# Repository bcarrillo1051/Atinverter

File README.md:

# Atinverter
Open Source DC to AC Inverter Documentation: https://bcarrillo1051.github.io/Atinverter/

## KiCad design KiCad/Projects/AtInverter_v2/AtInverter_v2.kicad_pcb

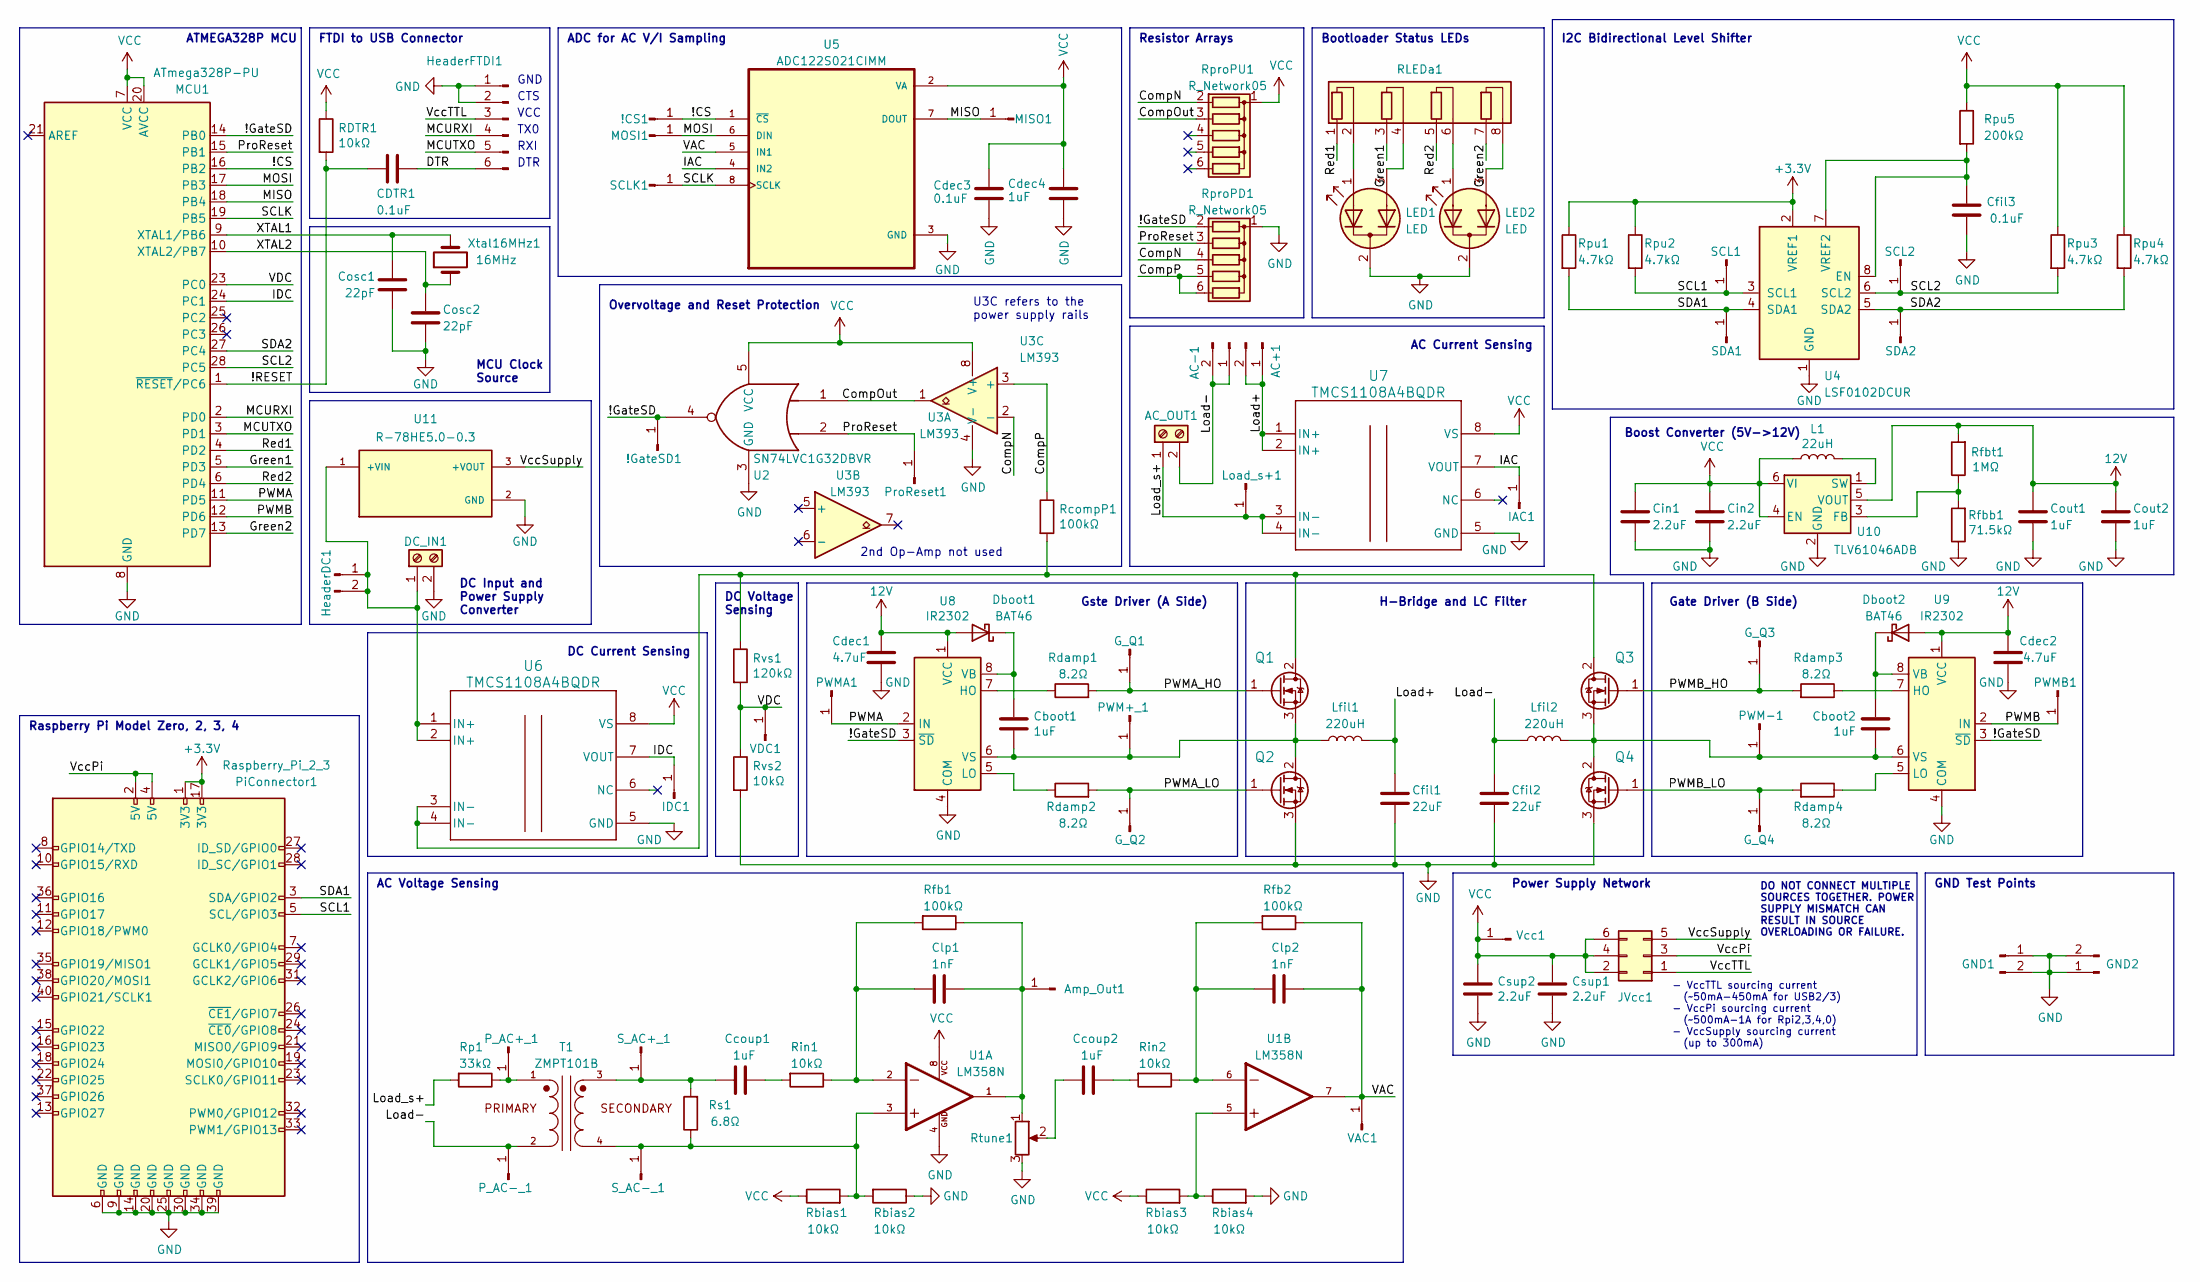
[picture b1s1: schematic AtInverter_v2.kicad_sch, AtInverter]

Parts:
!CS1: Conn_01x01_Male; PinHeader_1x01_P2.54mm_Vertical
!GateSD1: Conn_01x01_Male; PinHeader_1x01_P2.54mm_Vertical
AC+1: Conn_01x02_Pin; PinHeader_1x02_P2.54mm_Vertical
AC-1: Conn_01x02_Pin; PinHeader_1x02_P2.54mm_Vertical
AC_OUT1: Screw_Terminal_01x02; Term_Block_1x2_P5mm
Amp_Out1: Conn_01x01_Male; PinHeader_1x01_P2.54mm_Vertical
CDTR1: 0.1uF; C_1206_3216Metric
Cboot1, Cboot2: 1uF; C_0805_2012Metric
Ccoup1, Ccoup2: 1uF; C_1206_3216Metric
Cdec1, Cdec2: 4.7uF; C_1206_3216Metric
Cdec3: 0.1uF; C_0805_2012Metric
Cdec4: 1uF; C_0805_2012Metric
Cfil1, Cfil2: 22uF; CAP_BX_10x16_RUB
Cfil3: 0.1uF; C_1206_3216Metric
Cin1, Cin2: 2.2uF; C_0805_2012Metric
Clp1, Clp2: 1nF; C_1206_3216Metric
Cosc1, Cosc2: 22pF; C_1206_3216Metric
Cout1, Cout2: 1uF; C_0805_2012Metric
Csup1, Csup2: 2.2uF; C_1206_3216Metric
DC_IN1: Screw_Terminal_01x02; Term_Block_1x2_P5mm
Dboot1, Dboot2: BAT46; D_SOD-123
GND1, GND2: Conn_01x02_Pin; PinHeader_1x02_P2.54mm_Vertical
G_Q1, G_Q2, G_Q3, G_Q4: Conn_01x01_Male; PinHeader_1x01_P2.54mm_Vertical
HeaderDC1: Conn_01x02_Pin; PinHeader_1x02_P2.54mm_Vertical
HeaderFTDI1: Conn_01x06_Male; FTDI_USB_TTL_Header
IAC1: Conn_01x01_Male; PinHeader_1x01_P2.54mm_Vertical
IDC1: Conn_01x01_Male; PinHeader_1x01_P2.54mm_Vertical
JVcc1: Conn_02x03_Odd_Even; PinHeader_2x03_P2.54mm_Vertical
L1: 22uH; IND_BOURNS_SDR0403
LED1, LED2: LED; LED_3pin_P2.54mm
Lfil1, Lfil2: 220uH; AIRD-02_ABR
Load_s+1: Conn_01x01_Male; PinHeader_1x01_P2.54mm_Vertical
MCU1: ATmega328P-PU; DIP-28_W7.62mm_Socket
MISO1: Conn_01x01_Male; PinHeader_1x01_P2.54mm_Vertical
MOSI1: Conn_01x01_Male; PinHeader_1x01_P2.54mm_Vertical
PWM+_1: Conn_01x01_Male; PinHeader_1x01_P2.54mm_Vertical
PWM-1: Conn_01x01_Male; PinHeader_1x01_P2.54mm_Vertical
PWMA1: Conn_01x01_Male; PinHeader_1x01_P2.54mm_Vertical
PWMB1: Conn_01x01_Male; PinHeader_1x01_P2.54mm_Vertical
P_AC+_1: Conn_01x01_Male; PinHeader_1x01_P2.54mm_Vertical
P_AC-_1: Conn_01x01_Male; PinHeader_1x01_P2.54mm_Vertical
PiConnector1: Raspberry_Pi_2_3; Raspberry_Pi_Zero_and_Four
ProReset1: Conn_01x01_Male; PinHeader_1x01_P2.54mm_Vertical
Q1, Q2, Q3, Q4: IRFB4020PBF; TO-220-3_Vertical; MPN IRF540NPBF; Digi-Key_PN IRF540NPBF-ND
RDTR1: 10kΩ; R_1206_3216Metric
RLEDa1: R_Array; R_Array_SIP8
Rbias1, Rbias2, Rbias3, Rbias4: 10kΩ; R_1206_3216Metric
RcompP1: 100kΩ; R_1206_3216Metric
Rdamp1, Rdamp2, Rdamp3, Rdamp4: 8.2Ω; R_1206_3216Metric
Rfb1, Rfb2: 100kΩ; R_1206_3216Metric
Rfbb1: 71.5kΩ; R_0805_2012Metric
Rfbt1: 1MΩ; R_0805_2012Metric
Rin1, Rin2: 10kΩ; R_1206_3216Metric
Rp1: 33kΩ; R_1206_3216Metric
RproPD1: R_Network05; R_Array_SIP6
RproPU1: R_Network05; R_Array_SIP6
Rpu1, Rpu2, Rpu3, Rpu4: 4.7kΩ; R_1206_3216Metric
Rpu5: 200kΩ; R_1206_3216Metric
Rs1: 6.8Ω; R_1206_3216Metric
Rtune1: R_Potentiometer; TC33X-2-104E_BRN
Rvs1: 120kΩ; R_1206_3216Metric
Rvs2: 10kΩ; R_1206_3216Metric
SCL1, SCL2: Conn_01x01_Male; PinHeader_1x01_P2.54mm_Vertical
SCLK1: Conn_01x01_Male; PinHeader_1x01_P2.54mm_Vertical
SDA1, SDA2: Conn_01x01_Male; PinHeader_1x01_P2.54mm_Vertical
S_AC+_1: Conn_01x01_Male; PinHeader_1x01_P2.54mm_Vertical
S_AC-_1: Conn_01x01_Male; PinHeader_1x01_P2.54mm_Vertical
T1: ZMPT101B; XFMR_ZMPT101B; PARTREV NA
U1: LM358N; D8; PARTREV 1.0.3
U2: SN74LVC1G32DBVR; DBV5
U3: LM393; SO8_STM
U4: LSF0102DCUR; DCU0008A_L
U5: ADC122S021CIMM; MUA08A
U6, U7: TMCS1108A4BQDR; D0008A-IPC_A
U8, U9: IR2302; PG-DSO-8-910_INF
U10: TLV61046ADB; SOT-23-6
U11: R-78HE5.0-0.3; R-78HE-0.3_SIP3_11.5X8.5X12.5_RCP; PARTREV 0/2019
VAC1: Conn_01x01_Male; PinHeader_1x01_P2.54mm_Vertical
VDC1: Conn_01x01_Male; PinHeader_1x01_P2.54mm_Vertical
Vcc1: Conn_01x01_Male; PinHeader_1x01_P2.54mm_Vertical
Xtal16MHz1: 16MHz; Resonator-2Pin_W10.0mm_H5.0mm

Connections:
12V: Cdec1.1, Cdec2.1, Cout1.1, Cout2.1, Dboot1.2 (A), Dboot2.2 (A), Rfbt1.2, U8.1 (VCC), U9.1 (VCC), U10.5 (VOUT)
+3.3V: PiConnector1.1 (3V3), PiConnector1.17 (3V3), Rpu1.1, Rpu2.1, U4.2 (VREF1)
/!CS: !CS1.1, MCU1.16 (PB2), U5.1 (~CS)
/!GateSD: !GateSD1.1, MCU1.14 (PB0), RproPD1.2 (R1), U2.4, U8.3 (~SD), U9.3 (~SD)
/!RESET: CDTR1.2, MCU1.1 (~RESET/PC6), RDTR1.2
/CompN: RproPD1.4 (R3), RproPU1.2 (R1), U3.2 (-)
/CompOut: RproPU1.3 (R2), U2.1, U3.1
/CompP: RcompP1.1, RproPD1.5 (R4), RproPD1.6 (R5), U3.3 (+)
/DTR: CDTR1.1, HeaderFTDI1.6
/Green1: MCU1.5 (PD3), RLEDa1.3 (R2.1)
/Green2: MCU1.13 (PD7), RLEDa1.7 (R4.1)
/IAC: IAC1.1, U5.4 (IN2), U7.7 (VOUT)
/IDC: IDC1.1, MCU1.24 (PC1), U6.7 (VOUT)
/Load+: AC+1.1, AC+1.2, Cfil1.1, Lfil1.2, U7.1 (IN+), U7.2 (IN+)
/Load-: AC-1.1, AC-1.2, AC_OUT1.2, Cfil2.1, Lfil2.1, P_AC-_1.1, T1.2
/Load_s+: AC_OUT1.1, Load_s+1.1, Rp1.2, U7.3 (IN-), U7.4 (IN-)
/MCURXI: HeaderFTDI1.4, MCU1.2 (PD0)
/MCUTXO: HeaderFTDI1.5, MCU1.3 (PD1)
/MISO: MCU1.18 (PB4), MISO1.1, U5.7 (DOUT)
/MOSI: MCU1.17 (PB3), MOSI1.1, U5.6 (DIN)
/PWMA: MCU1.11 (PD5), PWMA1.1, U8.2 (IN)
/PWMA_HO: G_Q1.1, Q1.1 (G), Rdamp1.2
/PWMA_LO: G_Q2.1, Q2.1 (G), Rdamp2.2
/PWMB: MCU1.12 (PD6), PWMB1.1, U9.2 (IN)
/PWMB_HO: G_Q3.1, Q3.1 (G), Rdamp3.2
/PWMB_LO: G_Q4.1, Q4.1 (G), Rdamp4.2
/ProReset: MCU1.15 (PB1), ProReset1.1, RproPD1.3 (R2), U2.2
/Red1: MCU1.4 (PD2), RLEDa1.1 (R1.1)
/Red2: MCU1.6 (PD4), RLEDa1.5 (R3.1)
/SCL1: PiConnector1.5 (SCL/GPIO3), Rpu2.2, SCL1.1, U4.3 (SCL1)
/SCL2: MCU1.28 (PC5), Rpu3.2, SCL2.1, U4.6 (SCL2)
/SCLK: MCU1.19 (PB5), SCLK1.1, U5.8 (SCLK)
/SDA1: PiConnector1.3 (SDA/GPIO2), Rpu1.2, SDA1.1, U4.4 (SDA1)
/SDA2: MCU1.27 (PC4), Rpu4.2, SDA2.1, U4.5 (SDA2)
/VAC: Clp2.1, Rfb2.1, U1.7, U5.5 (IN1), VAC1.1
/VDC: MCU1.23 (PC0), Rvs1.2, Rvs2.1, VDC1.1
/VccPi: JVcc1.3, PiConnector1.2 (5V), PiConnector1.4 (5V)
/VccSupply: JVcc1.5, U11.3 (+VOUT)
/VccTTL: HeaderFTDI1.3, JVcc1.1
/XTAL1: Cosc1.2, MCU1.9 (XTAL1/PB6), Xtal16MHz1.2
/XTAL2: Cosc2.1, MCU1.10 (XTAL2/PB7), Xtal16MHz1.1
GND: Cdec1.2, Cdec2.2, Cdec3.2, Cdec4.2, Cfil1.2, Cfil2.2, Cfil3.1, Cin1.2, Cin2.2, Cosc1.1, Cosc2.2, Cout1.2, Cout2.2, Csup1.2, Csup2.2, DC_IN1.2, GND1.1, GND1.2, GND2.1, GND2.2, HeaderFTDI1.1, HeaderFTDI1.2, LED1.2 (K), LED2.2 (K), MCU1.8 (GND), MCU1.22 (GND), PiConnector1.6 (GND), PiConnector1.9 (GND), PiConnector1.14 (GND), PiConnector1.20 (GND), PiConnector1.25 (GND), PiConnector1.30 (GND), PiConnector1.34 (GND), PiConnector1.39 (GND), Q2.3 (S), Q4.3 (S), Rbias2.1, Rbias4.2, Rfbb1.1, RproPD1.1 (common), Rtune1.3, Rvs2.2, U1.4, U2.3 (GND), U3.4 (V-), U4.1 (GND), U5.3 (GND), U6.5 (GND), U7.5 (GND), U8.4 (COM), U9.4 (COM), U10.2 (GND), U11.2 (GND)
unnamed: Amp_Out1.1, Clp1.1, Rfb1.1, Rtune1.1, U1.1
unnamed: Ccoup1.1, Rin1.2
unnamed: Ccoup2.1, Rin2.2
unnamed: Ccoup2.2, Rtune1.2
unnamed: Clp1.2, Rfb1.2, Rin1.1, U1.2
unnamed: Clp2.2, Rfb2.2, Rin2.1, U1.6
unnamed: DC_IN1.1, HeaderDC1.1, HeaderDC1.2, U6.1 (IN+), U6.2 (IN+), U11.1 (+VIN)
unnamed: Cboot1.1, Dboot1.1 (K), U8.8 (VB)
unnamed: Cboot2.1, Dboot2.1 (K), U9.8 (VB)
unnamed: LED1.1 (A1), RLEDa1.2 (R1.2)
unnamed: LED1.3 (A2), RLEDa1.4 (R2.2)
unnamed: LED2.1 (A1), RLEDa1.6 (R3.2)
unnamed: LED2.3 (A2), RLEDa1.8 (R4.2)
unnamed: Cboot1.2, Lfil1.1, PWM+_1.1, Q1.3 (S), Q2.2 (D), U8.6 (VS)
unnamed: Cboot2.2, Lfil2.2, PWM-1.1, Q3.3 (S), Q4.2 (D), U9.6 (VS)
unnamed: P_AC+_1.1, Rp1.1, T1.1
unnamed: Q1.2 (D), Q3.2 (D), RcompP1.2, Rvs1.1, U6.3 (IN-), U6.4 (IN-)
unnamed: Rbias3.2, Rbias4.1, U1.5
unnamed: Ccoup1.2, Rs1.2, S_AC+_1.1, T1.3
unnamed: Rbias1.2, Rbias2.2, Rs1.1, S_AC-_1.1, T1.4, U1.3
unnamed: Cfil3.2, Rpu5.2, U4.7 (VREF2), U4.8 (EN)
unnamed: Rdamp1.1, U8.7 (HO)
unnamed: Rdamp2.1, U8.5 (LO)
unnamed: Rdamp3.1, U9.7 (HO)
unnamed: Rdamp4.1, U9.5 (LO)
unnamed: Rfbb1.2, Rfbt1.1, U10.3 (FB)
unnamed: L1.2, U10.1 (SW)
VCC: Cdec3.1, Cdec4.1, Cin1.1, Cin2.1, Csup1.1, Csup2.1, JVcc1.2, JVcc1.4, JVcc1.6, L1.1, MCU1.7 (VCC), MCU1.20 (AVCC), RDTR1.1, Rbias1.1, Rbias3.1, RproPU1.1 (common), Rpu3.1, Rpu4.1, Rpu5.1, U1.8, U2.5 (VCC), U3.8 (V+), U5.2 (VA), U6.8 (VS), U7.8 (VS), U10.4 (EN), U10.6 (VI), Vcc1.1

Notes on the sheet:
RXI
MCU Clock Source
ADC for AC V/I Sampling
AC Current Sensing
Overvoltage and Reset Protection
Power Supply Network
Boost Converter (5V->12V)
GND
ATMEGA328P MCU
Raspberry Pi Model Zero, 2, 3, 4
VCC
FTDI to USB Connector
DC Voltage Sensing
DO NOT CONNECT MULTIPLE SOURCES TOGETHER. POWER SUPPLY MISMATCH CAN RESULT IN SOURCE OVERLOADING OR FAILURE.
TX0
H-Bridge and LC Filter
AC Voltage Sensing
I2C Bidirectional Level Shifter
Gate Driver (B Side)
U3C refers to the power supply rails
DC Input and Power Supply Converter
- VccTTL sourcing current (~50mA-450mA for USB2/3) - VccPi sourcing current (~500mA-1A for Rpi2,3,4,0) - VccSupply sourcing current (up to 300mA)
DTR
Bootloader Status LEDs
CTS
2nd Op-Amp not used
Resistor Arrays
DC Current Sensing
GND Test Points
Gste Driver (A Side)

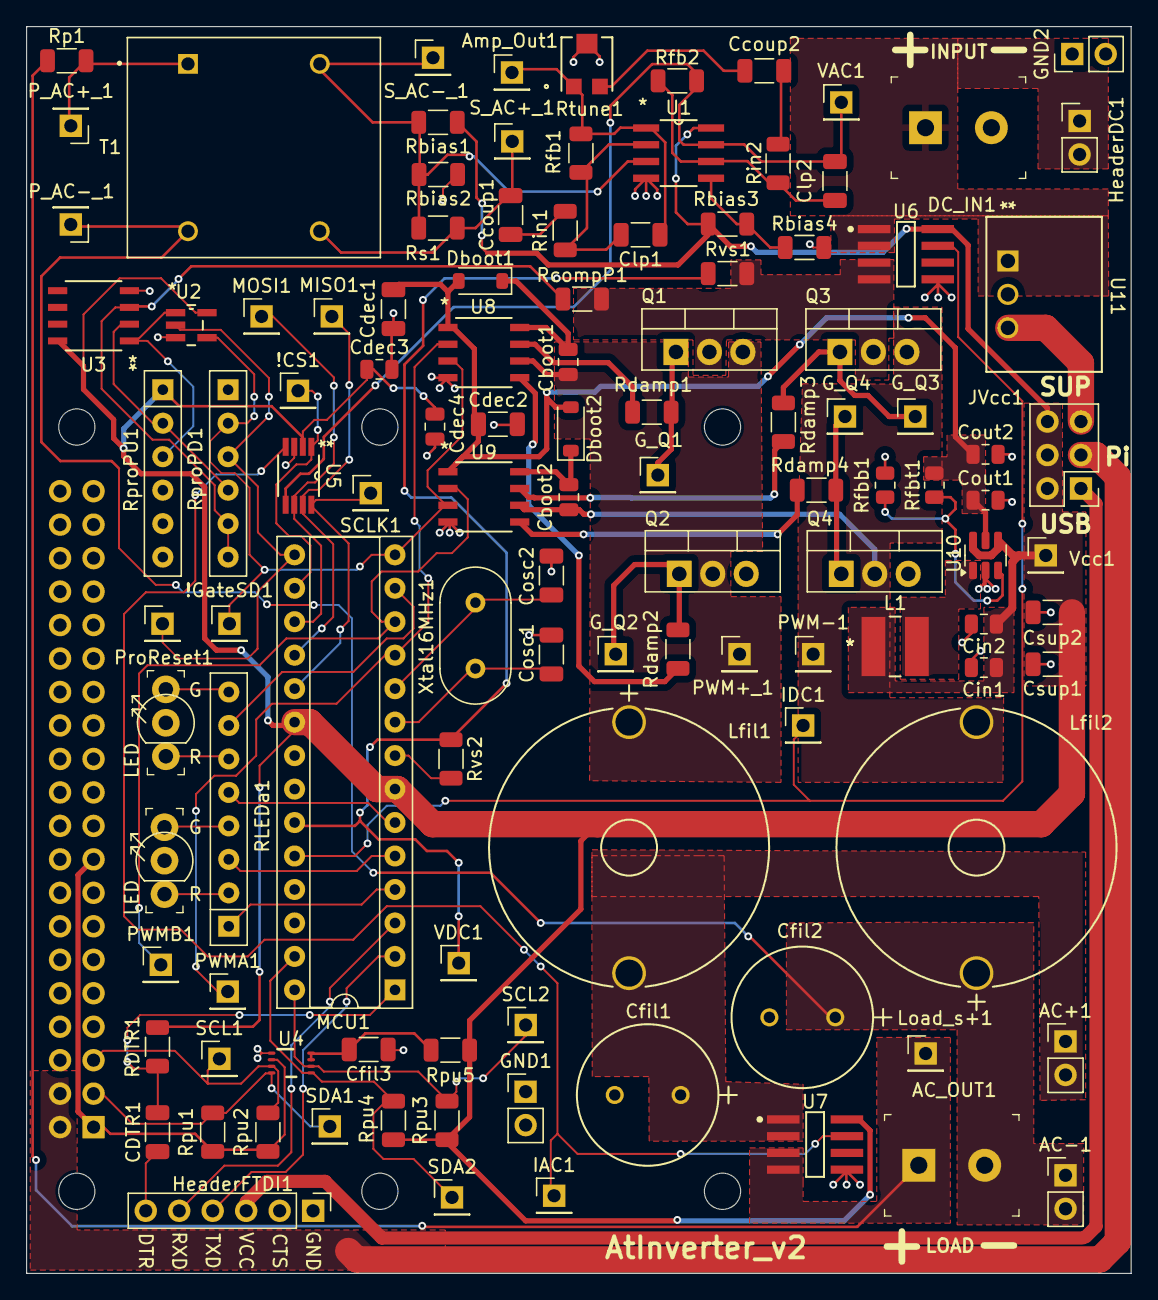
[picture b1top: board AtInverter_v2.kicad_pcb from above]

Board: 2 copper layers, 83.8 x 94.6 mm, 115 parts (1 on the bottom side), 70 nets.

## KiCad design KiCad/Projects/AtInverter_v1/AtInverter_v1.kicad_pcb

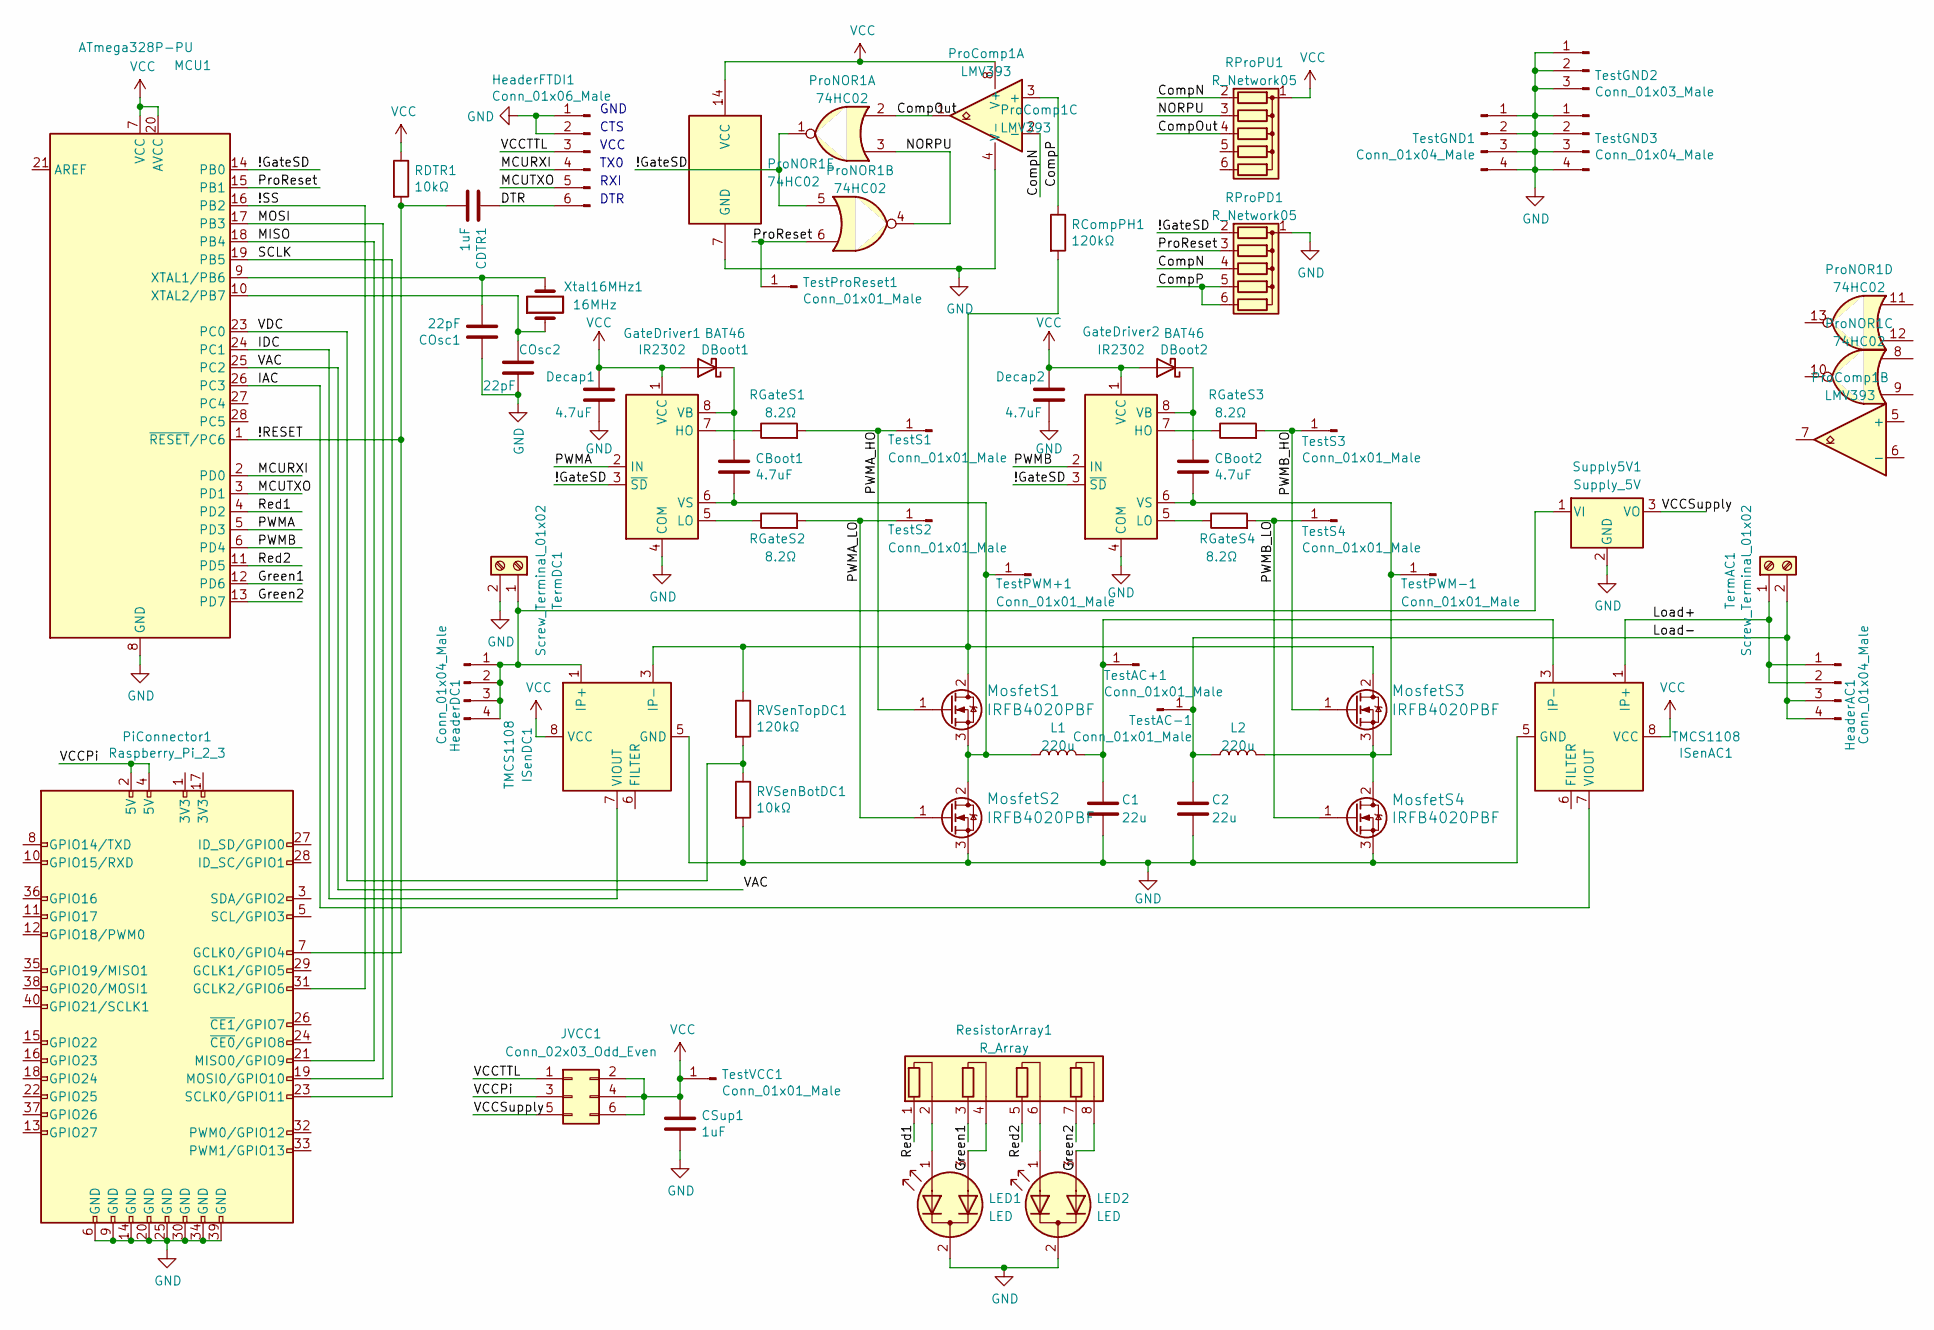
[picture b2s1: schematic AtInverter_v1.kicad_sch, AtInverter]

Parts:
C1, C2: 22u; CAP_BX_10x16_RUB
CBoot1, CBoot2: 4.7uF; C_Rect_L7.2mm_W3.5mm_P5.00mm_FKS2_FKP2_MKS2_MKP2
CDTR1: 1uF; C_Rect_L7.2mm_W3.5mm_P5.00mm_FKS2_FKP2_MKS2_MKP2
COsc1, COsc2: 22pF; C_Rect_L7.2mm_W3.5mm_P5.00mm_FKS2_FKP2_MKS2_MKP2
CSup1: 1uF; C_Rect_L7.2mm_W3.5mm_P5.00mm_FKS2_FKP2_MKS2_MKP2
DBoot1, DBoot2: BAT46; D_DO-35_SOD27_P7.62mm_Horizontal
Decap1, Decap2: 4.7uF; CAP_FG28_TDK
GateDriver1, GateDriver2: IR2302; DIP-8_W7.62mm_LongPads
HeaderAC1: Conn_01x04_Male; PinHeader_1x04_P2.54mm_Vertical
HeaderDC1: Conn_01x04_Male; PinHeader_1x04_P2.54mm_Vertical
HeaderFTDI1: Conn_01x06_Male; FTDI_USB_TTL_Header
ISenAC1: TMCS1108; SOIC-8_3.9x4.9mm_P1.27mm
ISenDC1: TMCS1108; SOIC-8_3.9x4.9mm_P1.27mm
JVCC1: Conn_02x03_Odd_Even; PinHeader_2x03_P2.54mm_Vertical
L1, L2: 220u; AIRD-02_ABR
LED1, LED2: LED; LED_3pin_P2.54mm
MCU1: ATmega328P-PU; DIP-28_W7.62mm
MosfetS1, MosfetS2, MosfetS3, MosfetS4: IRFB4020PBF; TO-220-3_Vertical; MPN IRF540NPBF; Digi-Key_PN IRF540NPBF-ND
PiConnector1: Raspberry_Pi_2_3; Raspberry_Pi_Zero_and_Four
ProComp1: LMV393; DIP-8_W7.62mm_LongPads
ProNOR1: 74HC02; DIP-14_W7.62mm_LongPads
RCompPH1: 120kΩ; R_Axial_DIN0207_L6.3mm_D2.5mm_P7.62mm_Horizontal
RDTR1: 10kΩ; R_Axial_DIN0207_L6.3mm_D2.5mm_P7.62mm_Horizontal
RGateS1, RGateS2, RGateS3, RGateS4: 8.2Ω; R_Axial_DIN0207_L6.3mm_D2.5mm_P7.62mm_Horizontal
RProPD1: R_Network05; R_Array_SIP6
RProPU1: R_Network05; R_Array_SIP6
RVSenBotDC1: 10kΩ; R_Axial_DIN0207_L6.3mm_D2.5mm_P7.62mm_Horizontal
RVSenTopDC1: 120kΩ; R_Axial_DIN0207_L6.3mm_D2.5mm_P7.62mm_Horizontal
ResistorArray1: R_Array; R_Array_SIP8
Supply5V1: Supply_5V; SupplyDC_48V-5V_TO-220-3_Vertical
TermAC1: Screw_Terminal_01x02; Term_Block_1x2_P5mm
TermDC1: Screw_Terminal_01x02; Term_Block_1x2_P5mm
TestAC+1: Conn_01x01_Male; PinHeader_1x01_P2.54mm_Vertical
TestAC-1: Conn_01x01_Male; PinHeader_1x01_P2.54mm_Vertical
TestGND1, TestGND3: Conn_01x04_Male; PinHeader_1x04_P2.54mm_Vertical
TestGND2: Conn_01x03_Male; PinHeader_1x03_P2.54mm_Vertical
TestPWM+1: Conn_01x01_Male; PinHeader_1x01_P2.54mm_Vertical
TestPWM-1: Conn_01x01_Male; PinHeader_1x01_P2.54mm_Vertical
TestProReset1: Conn_01x01_Male; PinHeader_1x01_P2.54mm_Vertical
TestS1, TestS2, TestS3, TestS4: Conn_01x01_Male; PinHeader_1x01_P2.54mm_Vertical
TestVCC1: Conn_01x01_Male; PinHeader_1x01_P2.54mm_Vertical
Xtal16MHz1: 16MHz; Resonator-2Pin_W10.0mm_H5.0mm

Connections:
/!GateSD: GateDriver1.3 (~SD), GateDriver2.3 (~SD), MCU1.14 (PB0), ProNOR1.1, ProNOR1.5, RProPD1.2 (R1)
/!RESET: CDTR1.2, MCU1.1 (~RESET/PC6), PiConnector1.7 (GCLK0/GPIO4), RDTR1.2
/!SS: MCU1.16 (PB2), PiConnector1.31 (GCLK2/GPIO6)
/CompN: ProComp1.2 (-), RProPD1.4 (R3), RProPU1.2 (R1)
/CompOut: ProComp1.1, ProNOR1.2, RProPU1.4 (R3)
/CompP: ProComp1.3 (+), RCompPH1.1, RProPD1.5 (R4), RProPD1.6 (R5); also elsewhere on the board
/DTR: CDTR1.1, HeaderFTDI1.6
/Green1: MCU1.12 (PD6), ResistorArray1.3 (R2.1)
/Green2: MCU1.13 (PD7), ResistorArray1.7 (R4.1)
/IAC: ISenAC1.7 (VIOUT), MCU1.26 (PC3)
/IDC: ISenDC1.7 (VIOUT), MCU1.24 (PC1)
/Load+: HeaderAC1.1, HeaderAC1.2, ISenAC1.1 (IP+), ISenAC1.2 (IP+), TermAC1.1
/Load-: C2.1, HeaderAC1.3, HeaderAC1.4, L2.1, TermAC1.2, TestAC-1.1
/MCURXI: HeaderFTDI1.4, MCU1.2 (PD0)
/MCUTXO: HeaderFTDI1.5, MCU1.3 (PD1)
/MISO: MCU1.18 (PB4), PiConnector1.21 (MISO0/GPIO9)
/MOSI: MCU1.17 (PB3), PiConnector1.19 (MOSI0/GPIO10)
/NORPU: ProNOR1.3, ProNOR1.4, RProPU1.3 (R2)
/PWMA: GateDriver1.2 (IN), MCU1.5 (PD3)
/PWMA_HO: MosfetS1.1 (G), RGateS1.2, TestS1.1
/PWMA_LO: MosfetS2.1 (G), RGateS2.2, TestS2.1
/PWMB: GateDriver2.2 (IN), MCU1.6 (PD4)
/PWMB_HO: MosfetS3.1 (G), RGateS3.2, TestS3.1
/PWMB_LO: MosfetS4.1 (G), RGateS4.2, TestS4.1
/ProReset: MCU1.15 (PB1), ProNOR1.6, RProPD1.3 (R2), TestProReset1.1
/Red1: MCU1.4 (PD2), ResistorArray1.1 (R1.1)
/Red2: MCU1.11 (PD5), ResistorArray1.5 (R3.1)
/SCLK: MCU1.19 (PB5), PiConnector1.23 (SCLK0/GPIO11)
/VAC: MCU1.25 (PC2)
/VCCPi: JVCC1.3, PiConnector1.2 (5V), PiConnector1.4 (5V)
/VCCSupply: JVCC1.5, Supply5V1.3 (VO)
/VCCTTL: HeaderFTDI1.3, JVCC1.1
/VDC: MCU1.23 (PC0), RVSenBotDC1.1, RVSenTopDC1.2
GND: C1.2, C2.2, COsc1.1, COsc2.2, CSup1.2, Decap1.2, Decap2.2, GateDriver1.4 (COM), GateDriver2.4 (COM), HeaderFTDI1.1, HeaderFTDI1.2, ISenAC1.5 (GND), ISenDC1.5 (GND), LED1.2 (K), LED2.2 (K), MCU1.8 (GND), MCU1.22 (GND), MosfetS2.3 (S), MosfetS4.3 (S), PiConnector1.6 (GND), PiConnector1.9 (GND), PiConnector1.14 (GND), PiConnector1.20 (GND), PiConnector1.25 (GND), PiConnector1.30 (GND), PiConnector1.34 (GND), PiConnector1.39 (GND), ProComp1.4 (V-), ProNOR1.7 (GND), RProPD1.1 (common), RVSenBotDC1.2, Supply5V1.2 (GND), TermDC1.2, TestGND1.1, TestGND1.2, TestGND1.3, TestGND1.4, TestGND2.1, TestGND2.2, TestGND2.3, TestGND3.1, TestGND3.2, TestGND3.3, TestGND3.4
unnamed: CBoot1.1, DBoot1.1 (K), GateDriver1.8 (VB)
unnamed: CBoot2.1, DBoot2.1 (K), GateDriver2.8 (VB)
unnamed: GateDriver1.7 (HO), RGateS1.1
unnamed: GateDriver1.5 (LO), RGateS2.1
unnamed: CBoot1.2, GateDriver1.6 (VS), L1.1, MosfetS1.3 (S), MosfetS2.2 (D), TestPWM+1.1
unnamed: GateDriver2.7 (HO), RGateS3.1
unnamed: GateDriver2.5 (LO), RGateS4.1
unnamed: CBoot2.2, GateDriver2.6 (VS), L2.2, MosfetS3.3 (S), MosfetS4.2 (D), TestPWM-1.1
unnamed: HeaderDC1.1, HeaderDC1.2, HeaderDC1.3, HeaderDC1.4, ISenDC1.1 (IP+), ISenDC1.2 (IP+), Supply5V1.1 (VI), TermDC1.1
unnamed: LED1.1 (A1), ResistorArray1.2 (R1.2)
unnamed: LED1.3 (A2), ResistorArray1.4 (R2.2)
unnamed: LED2.1 (A1), ResistorArray1.6 (R3.2)
unnamed: LED2.3 (A2), ResistorArray1.8 (R4.2)
unnamed: COsc1.2, MCU1.9 (XTAL1/PB6), Xtal16MHz1.2
unnamed: COsc2.1, MCU1.10 (XTAL2/PB7), Xtal16MHz1.1
unnamed 49: ISenDC1.3 (IP-), ISenDC1.4 (IP-), MosfetS1.2 (D), MosfetS3.2 (D), RCompPH1.2, RVSenTopDC1.1; also elsewhere on the board
unnamed: C1.1, ISenAC1.3 (IP-), ISenAC1.4 (IP-), L1.2, TestAC+1.1
VCC: CSup1.1, DBoot1.2 (A), DBoot2.2 (A), Decap1.1, Decap2.1, GateDriver1.1 (VCC), GateDriver2.1 (VCC), ISenAC1.8 (VCC), ISenDC1.8 (VCC), JVCC1.2, JVCC1.4, JVCC1.6, MCU1.7 (VCC), MCU1.20 (AVCC), ProComp1.8 (V+), ProNOR1.14 (VCC), RDTR1.1, RProPU1.1 (common), TestVCC1.1

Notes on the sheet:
RXI
GND
VCC
TX0
DTR
CTS

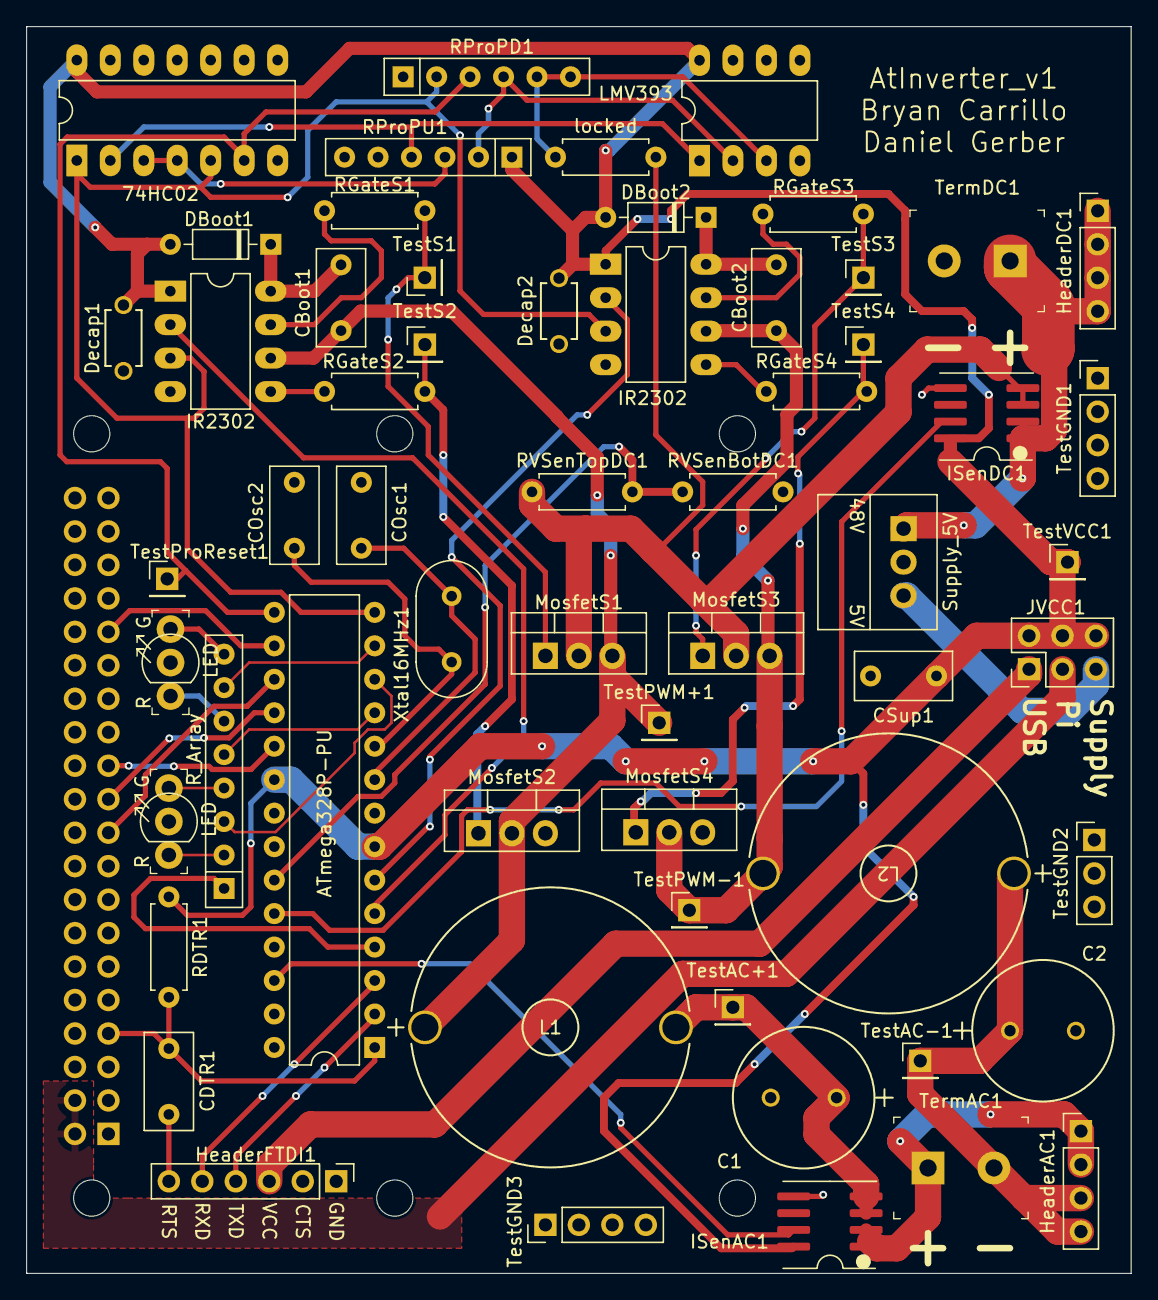
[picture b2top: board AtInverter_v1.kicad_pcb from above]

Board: 2 copper layers, 83.8 x 94.6 mm, 60 parts (1 on the bottom side), 51 nets.

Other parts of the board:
locked: 120kΩ; R_Axial_DIN0207_L6.3mm_D2.5mm_P7.62mm_Horizontal

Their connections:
/CompP: locked.1; also elsewhere on the board
unnamed 49: locked.2; also elsewhere on the board

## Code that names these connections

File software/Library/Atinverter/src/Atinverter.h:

/*
	Atinverter.h = Library for Atinverter pin and functions
  	Created by Bryan Carrillo, Zach Kwast, 10/18/24
	Released into the public domain (Open Source DC to AC Inverter)
*/

#ifndef ATINVERTER_H
#define ATINVERTER_H

#include <Arduino.h>
#include <SPI.h>

// --- TMCS1108 Current Sensor Parameters ---
#define SENSOR_GAIN_MV_PER_A 400.0f // Sensitivity for A4 variant (400 mV per A)
#define MV_TO_V 0.001f // Scaling factor from mV to V
#define VOUT_0A 2.5f // Zero current output voltage

// --- ADC Parameters ---
#define VREF 5.0f // Reference voltage for both ADCs
#define ADC_ATMEGA328P_MAX_VALUE 1023.0f // For ATMEGA328P (internal ADC)
#define ADC_122S021_MAX_VALUE 4095.0f // For ADC122S021 (external SPI ADC)
#define VAC_ADC_CHANNEL 0x00 // ADC122S021 channel 1
#define IAC_ADC_CHANNEL 0x08 // ADC122S021 channel 2
#define CLOCK_FREQUENCY 1000000 // Clock used to drive ADC122S021

// --- AC RMS Parameters ---
#define MS_PER_SECOND 1000 // For computing the sampling period in ms
#define DEFAULT_SENSITIVITY 500.0f // When no sensitivity is specified for AC RMS calculation
#define SENSITIVITY 38.12f // Tuned value after testing, adjust as needed

// --- Moving Average Parameter ---
#define MA_SAMPLES 10 // Default moving average sample count, adjust as needed

// --- PWM Inversion Parameters ---
#define SIN_50HZ_PWM_SIZE 313
#define SIN_60HZ_PWM_SIZE 260

// --- Safety Parameters ---
#define MAX_DC_CURRENT 2.5
#define MAX_AC_CURRENT 2.5

// shutdown error codes for convenience and bookkeeping. user-defined codes start at 4
enum ShutdownCodes
{
  // is not shut down = -1
  HARDWARE = 0,
  MANUAL = 1,
  OVERCURRENT = 2,
  OVERTEMPERATURE = 3,
  NUM_PRESETCODES
};

/**
 * @class Atinverter
 * @brief This class handles the control of the Atinverter, including pin setup
 *        and LED management.
 */
class Atinverter {

  public:
  	// - Constructor -

	Atinverter();

	// - Methods -

	// --- LED Blinking ---
	void setUpLEDs();
	void set1LED(int led, int state);
	void cycleLEDs(int t_delay);
	
	// --- DC Voltage and Current Sensing ---
	float getVdc();
	float getIdc();
	float getAvgDC(bool isVdc, float signalValue);

	// --- AC Voltage and Current Sensing ---
	void setUpSPI();
	void setSensitivity(float value);
	int getADC(uint8_t control_byte);
	float getRmsAC(bool isVac, uint8_t loopCount);

	// --- PWM 50Hz/60Hz Inversion ---
	void startPWM(uint16_t frequency);
	static void pwmISR();
	void enablePWM();
	void disablePWM();

	// --- Timer 2 Delay ---
	void initTimer2Delay();
	void delay2(unsigned long ms);
	unsigned long millis2();

	// --- Gate Shutdown ---
	void shutdownGates(int shutdownCode);
	void turnOnGates();
	void powerCycleGates();

	// --- Overcurrent Protection ---
	void checkOverCurrent(float dcCurrent, float acCurrent);

	// - Member Variables -

	// --- LED Blinking ---
	static const int LED1R_PIN = 2; // Red LED 1 pin | PD2
	static const int LED1G_PIN = 3; // Green LED 1 pin | PD3
	static const int LED2R_PIN = 4; // Red LED 2 pin | PD4
	static const int LED2G_PIN = 7; // Green LED 2 pin | PD7

	// --- Timer 2 Delay ---
	static volatile unsigned long timer2Millis; // Timer2 Increment

  private:

	// - Methods -

	// --- AC Voltage and Current Sensing ---
	int getZeroPoint(uint8_t control_byte);

	// - Member Variables -

	// --- AC Voltage and Current Sensing ---
	// Pin Definitions
	static const int VI_AC_CS_PIN = 10;   // SPI chip select pin | PB2
	static const int VI_AC_MOSI_PIN = 11; // Send control bits data pin | PB3
	static const int VI_AC_MISO_PIN = 12; // Receive AC output V/I sense pin | PB4
	static const int VI_AC_SCLK_PIN = 13; // SPI clock signal pin | PB5

	// Parameters AC Sensing
	uint32_t period; // Period of PWM type (50Hz or 60Hz)
	float 	 sensitivity = DEFAULT_SENSITIVITY; // Tune this value to achieve proper sensing

	// --- DC Voltage and Current Sensing ---
	// DC Voltage and Current Pin Definitions
	static const int V_DC_PIN = A0;           // DC input voltage sense pin | PC0
	static const int I_DC_PIN = A1;           // DC input current sense pin | PC1
	// DC Voltage Sensing Resistor Values
	static const unsigned long Rvs1 = 120000; // DC voltage sensing resistor 1, adjust as needed
	static const unsigned int Rsv2 = 9900;    // DC voltage sensing resistor 2, adjust as needed
	// Parameters for Vdc Moving Average
	static const int Vdc_num_readings = MA_SAMPLES; // Vdc samples in moving average
	float Vdc_readings[MA_SAMPLES];                 // Circular buffer for Vdc samples
	int Vdc_read_index = 0;                         // Current index in the Vdc buffer
	float Vdc_total = 0;                            // Running total of Vdc readings
	// Parameters for Idc Moving Average
	static const int Idc_num_readings = MA_SAMPLES; // Idc damples in moving average
	float Idc_readings[MA_SAMPLES];                 // Circular buffer for Idc samples
	int Idc_read_index = 0;                         // Current index in the Idc buffer
	float Idc_total = 0;                            // Running total of Idc readings

	// --- PWM 50Hz/60Hz Inversion ---
	// PWM Pin Definitions=
	const int PWM_A_PIN = 5;    // Positive half cycle PWM pin | PD5
	const int PWM_B_PIN = 6;    // Negative half cycle PWM pin | PD6
	const int GATESD_PIN = 8;   // Gate driver shut down mechanism pin | PB0
	const int PRORESET_PIN = 9; // Protection circuitry reset pin | PB1
	// Parameters for PWM
	static bool is50Hz;               // Frequency mode: true for 50Hz, false for 60Hz
	static int sin_i;                 // Index for sinPWM array value
	static int pwm_i;                 // Index for PWM value
	static int OK;                    // Flag to toggle between pins 5 and 6
	static const int sin50HzPWM[312]; // Sinusoidal 50Hz array samples
	static const int sin60HzPWM[261]; // Sinusoidal 60Hz array samples

	// --- I2C Communication ---
	const int I2C_SDA_PIN = A4;  // Data line between ATMEGA328P and Raspberry Pi pin | PC4
	const int I2C_SCL_PIN = A5;  // Clock line between ATMEGA328P and Raspberry Pi pin | PC5

	// --- Gate Shutdown ---
	int _shutdownCode = 0;
};

#endif

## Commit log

2024-04-24 License for Open Source
    License to acknowledge that this GitHub repository is to be shared by any user and its contents can be utilized freely.
2024-04-24 Update LICENSE
    Updated license with proper school and developer
2024-04-24 Update LICENSE
    Fixed the name of the type of license
2024-04-24 AtinverterE KICAD and Programming Directories
2024-04-25 Atinverter V1 BOM
    Build of Materials for the 1st iteration of the DC to AC inverter design for the Microgrid PDA
2024-05-16 Created config file to use Cayman theme for GitHub Pages
2024-05-16 Rename _config.yaml to _config.yml
2024-05-16 index.html file test
2024-05-16 Hopefully fixed html to work with Cayman theme
2024-05-16 Add website link to README and title edit for index.html
2024-05-16 Attempt to remove the extra line for the Cayman theme
2024-05-16 Added gemfile to allow real time editting of website on local machine
2024-05-17 remove Atinverter autosave BOM
2024-06-03 commented 50 and 60Hz PWM inverter files, added hardware.html file and added 'Hardware' button that creates hardware documententation page for web page
2024-06-04 Updated Title of website
2024-09-19 don't recall changes, probably minor
2024-09-19 Template files were added to set up for JustTheDocs website theme
2024-09-19 Fixed failed ci.yml test
2024-09-20 Fixed typo in pages.yml
2024-10-17 Changed footprint for IR2302 to SMD
2024-10-18 Removed unnecessary AtinverterE class definition from blink code and addes Doxygen comments to many files. Developed template for AtinverterE.cpp
2025-01-08 Preliminary website design with basic pages
2025-01-28 Vision Page Baseline Done
2025-01-28 Create index.md file for home page
2025-01-28 Fixed picture rendering bug
2025-01-28 Fixed link rendering bug
2025-01-28 Fixed link rendering bug 2
2025-01-28 Fixed link rendering bug 3
2025-03-24 Restructured file hierarchy for clarity
2025-03-25 Editted pin mapping in class, modified blink code, fully functioning
2025-03-25 Created documentation for Atinverter library set up, developed a working Vdc sensing code, verified
2025-03-27 Completed the Vdc sensing code
2025-03-27 Improved readability of Vdc_Sensing.ino and wrote baseline Idc_Sensing.ino code
2025-03-27 modified kicad folder name from KiCad to kicad for consistency of lowercase folders
2025-03-29 Converted procedural code of Vdc and Idc sensing to object oriented code
2025-03-30 Updated Library code with OOP PWM, preliminary Vac code
2025-03-31 Updated Lib code, obtained many captures of device, stopped at readADC dev
2025-04-04 Updated sensing code, website editted
2025-04-04 Beginning of Main File creation
2025-04-04 Restructured file hierarchy of Atinverter lib and included ZMPT101B lib
2025-04-05 Added AC sensing Code
2025-04-07 Improved commenting of code, consolidated readAvgVdc() and readAvgIdc() to readAvg(), added timer2 delay code and new timer2 section for website
2025-04-07 Began documenting timer2 delay code
2025-04-08 Added finished ZMPT101B code and updated Atinverter lib
2025-04-09 Preliminary main function design
2025-04-09 Debugged compiler errors
2025-04-09 ZMPT101B lib fix
2025-04-10 Finished Debugging with hardware
2025-04-14 Added dedicated section for hardware description and high level diagrams
2025-04-14 Modified getAvg() method to now be compatible with both Vdc and Idc
2025-04-14 Commented the methods of Atinverter.h
2025-04-14 Changed values for testing
2025-04-15 Fixed max current values
2025-04-15 Updated Based on Library changes
2025-04-17 modifications to a_v2 hardware docs section
2025-04-17 Modified a_v2 hardware docs file, almost done
2025-04-17 Completed Iac code, needs verification, adjusted VI sensing files to reflect changes in AC sensing and DC sensing
2025-04-21 Organized simulation files, created template for software lib and modules doc, finalized AC voltage sensor ltspice sim, and further dev to hardware atinverter v2 description
2025-04-21 Minor edit to modules hierarchy
2025-04-22 Completed software tab and modified block diagram to be more compact and interact for all nodes of current design
2025-04-22 fixed power cycle gate driver function, updated Main
2025-04-22 Updated States
2025-04-23 Fixed merge conflicts
2025-04-24 Cleaned up main code, added gate turn on function
2025-04-24 Fixed missing if statement for ADC channel selection
2025-04-24 Removed sensitivity #define from Vac_sensing.ino since already in Atinverter.h
2025-04-24 Remove SPI.h include since its already included in the Atinverter.h header, also removed sensitivity parameter from Iac_Sensing.ino since aleady in Atinverter.h
2025-04-24 changed Arduino.h to <Arduino.h>
2025-04-29 Blink and DC V/I software documentation complete
2025-04-30 Organized library file documentation
2025-04-30 Coding documentation nearly done, just need to finish PWM_inversion_feature
2025-05-01 Added section for PWM inversion feature
2025-05-01 Finished software documenation for website
2025-05-01 Reorganized atinverter v2 hardware section
2025-05-02 organized hw documentation into various sections
2025-05-02 Removed all Serial communication to eliminate power cycle bug
2025-05-02 Reduced redudancy of startPWM method, no need to specify PWM flag
2025-05-02 Modified the website to reflect startPWM() changes
2025-05-03 Altered the PWM function calls
2025-05-07 Completed Overvoltage and Reset Protection Hardware Section
2025-05-08 Completed Boost Converter hardware documentation
2025-05-10 Experiementation section preliminary
2025-05-13 Removed constructor frequency parameter and delegated the PWM inversion fundamental frequency setting to startPWM(), documentation also updated accordingly
2025-05-14 Added a macro to describe pwm sinusoid arrays for readability
2025-05-19 Completed and verified AC current sensing code
2025-05-23 fixed Idc computation in getIdc()
2025-05-26 Eliminated PWM on startup
2025-05-27 Added Microgrid interfacing files
2025-05-28 Added comments and updated README
2025-06-09 Upaded Headers and Comments
